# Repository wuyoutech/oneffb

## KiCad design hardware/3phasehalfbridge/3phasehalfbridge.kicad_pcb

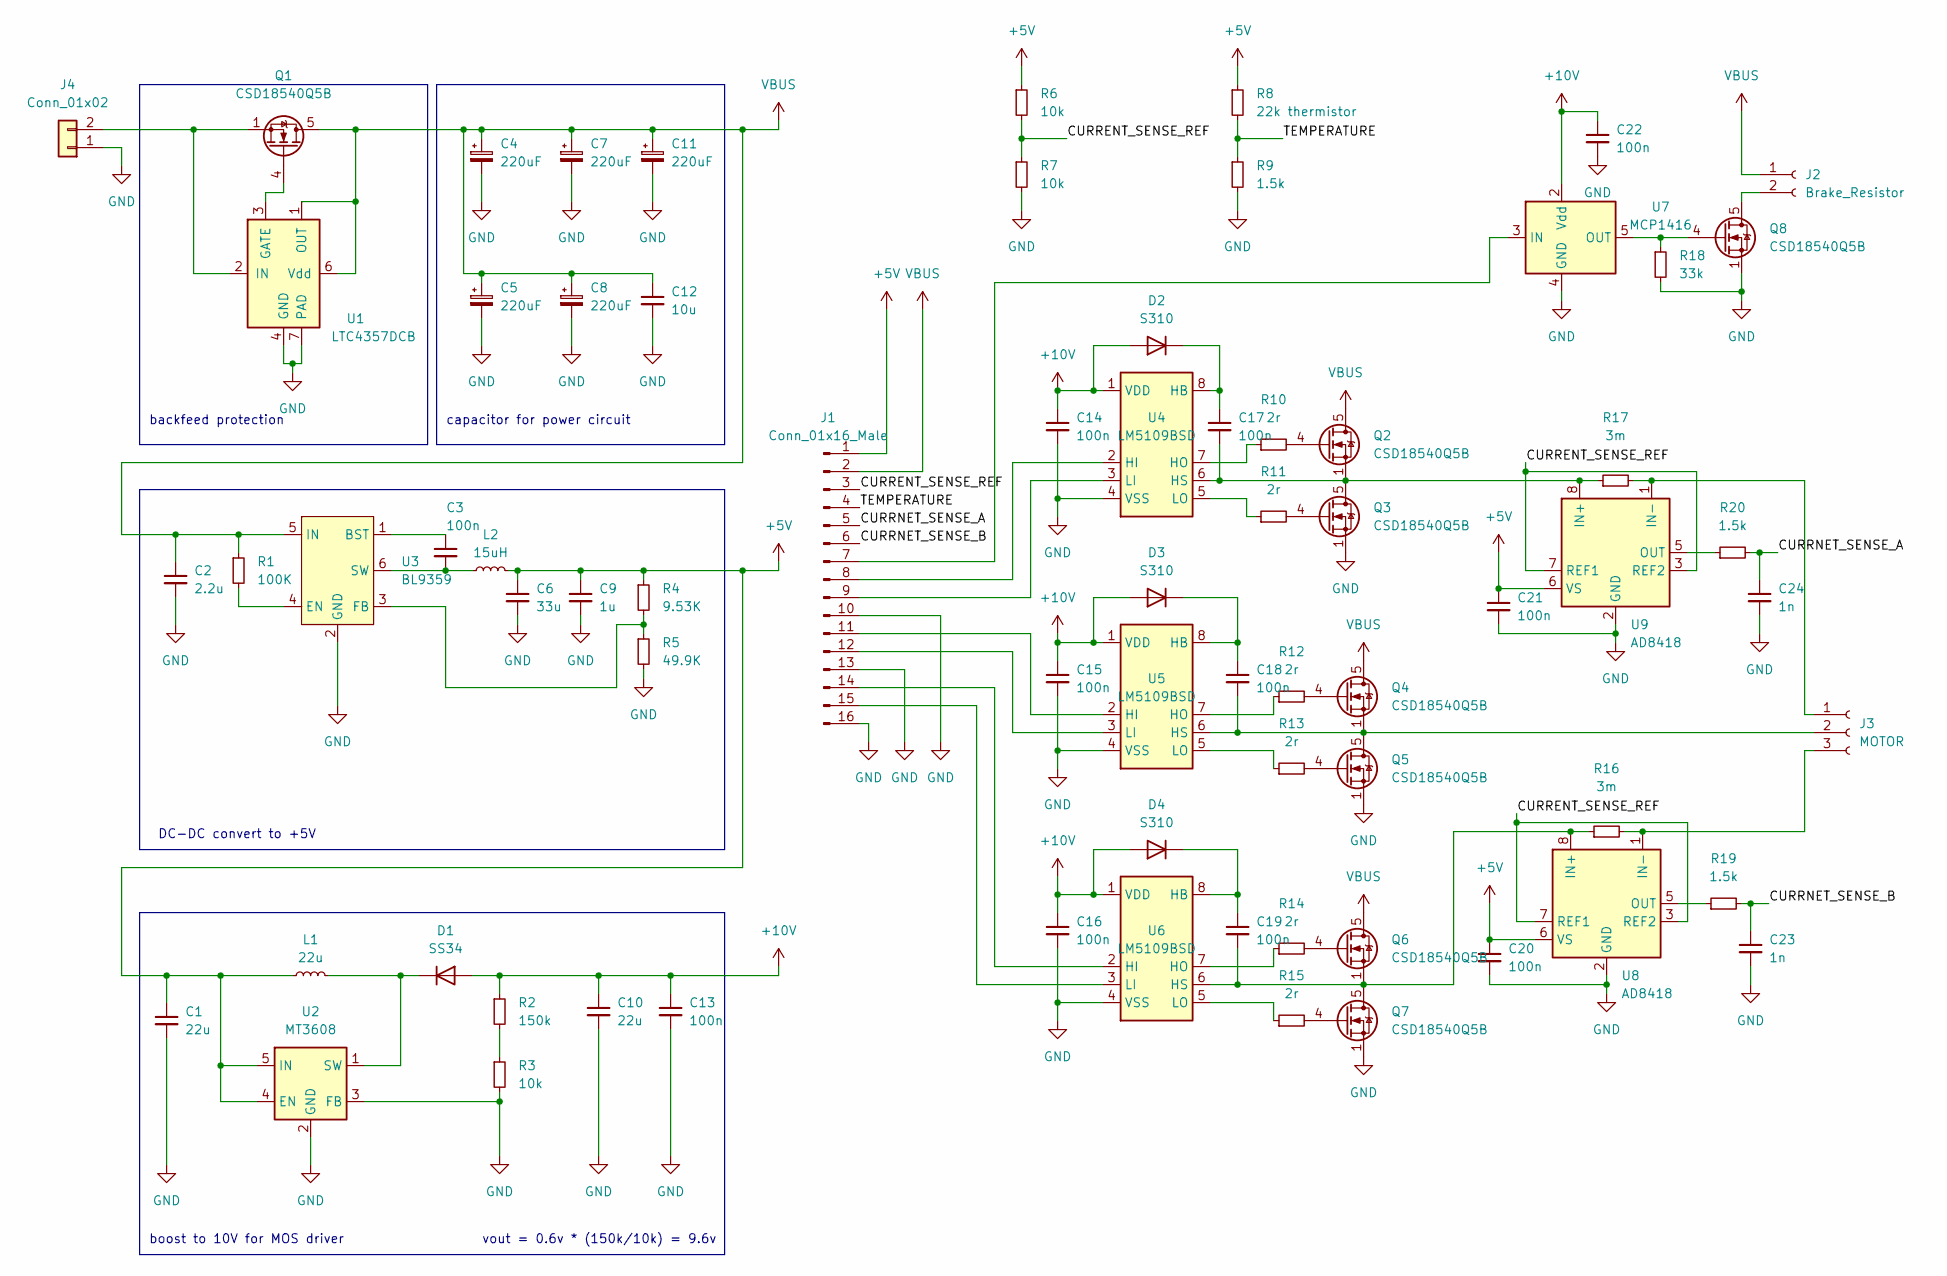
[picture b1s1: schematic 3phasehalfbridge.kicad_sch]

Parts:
C1: 22u; C_0805_2012Metric
C2: 2.2u; C_0805_2012Metric
C3, C13, C14, C15, C16, C17, C18, C19, C20, C21, C22: 100n; C_0402_1005Metric
C4, C5, C7, C8, C11: 220uF; CP_Elec_6.3x3.9
C6: 33u; C_0805_2012Metric
C9: 1u; C_0402_1005Metric
C10: 22u; C_0603_1608Metric
C12: 10u; C_0603_1608Metric
C23, C24: 1n; C_0402_1005Metric
D1: SS34; D_SOD-123F
D2, D4: S310; D_SOD-123F
D3: S310; D_DO-41_SOD81_P10.16mm_Horizontal
J1: Conn_01x16_Male; PinHeader_1x16_P2.54mm_Vertical
J2: Brake_Resistor; SolderWire-1.5sqmm_1x02_P7.8mm_D1.7mm_OD3.9mm
J3: MOTOR; AMASS_MR30PW-FB_1x03_P3.50mm_Horizontal
J4: Conn_01x02; AMASS_XT30PW-M_1x02_P2.50mm_Horizontal
L1: 22u; L_Taiyo-Yuden_MD-5050
L2: 15uH; L_Taiyo-Yuden_MD-5050
Q1, Q2, Q3, Q4, Q5, Q6, Q7, Q8: CSD18540Q5B; TDSON-8-1
R1: 100K; R_0402_1005Metric
R2: 150k; R_0402_1005Metric
R3, R6, R7: 10k; R_0402_1005Metric
R4: 9.53K; R_0402_1005Metric
R5: 49.9K; R_0402_1005Metric
R8: 22k thermistor; R_0402_1005Metric
R9, R19, R20: 1.5k; R_0402_1005Metric
R10, R11, R12, R13, R14, R15: 2r; R_0402_1005Metric
R16, R17: 3m; R_2512_6332Metric
R18: 33k; R_0402_1005Metric
U1: LTC4357DCB; DFN-6-1EP_3x2mm_P0.5mm_EP1.65x1.35mm
U2: MT3608; SOT-23-6
U3: BL9359; SOT-23-6
U4, U5, U6: LM5109BSD; WSON-8-1EP_4x4mm_P0.8mm_EP2.6x3mm
U7: MCP1416; SOT-23-5
U8, U9: AD8418; MSOP-8_3x3mm_P0.65mm

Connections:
+5V: C1.1, C6.1, C9.1, C20.1, C21.1, J1.1, L1.1, L2.2, R4.1, R6.1, R8.1, U2.4 (EN), U2.5 (IN), U8.6 (VS), U9.6 (VS)
+10V: C10.1, C13.1, C14.1, C15.1, C16.1, C22.1, D1.2 (A), D2.2 (A), D3.2 (A), D4.2 (A), R2.1, U4.1 (VDD), U5.1 (VDD), U6.1 (VDD), U7.2 (Vdd)
/CURRENT_SENSE_REF: J1.3, R6.2, R7.1, U8.3 (REF2), U8.7 (REF1), U9.3 (REF2), U9.7 (REF1)
/CURRNET_SENSE_A: C24.1, J1.5, R20.2
/CURRNET_SENSE_B: C23.1, J1.6, R19.2
/TEMPERATURE: J1.4, R8.2, R9.1
GND: C1.2, C2.2, C4.2, C5.2, C6.2, C7.2, C8.2, C9.2, C10.2, C11.2, C12.2, C13.2, C14.2, C15.2, C16.2, C20.2, C21.2, C22.2, C23.2, C24.2, J1.10, J1.13, J1.16, J4.1, Q3.1 (S), Q3.2 (S), Q3.3 (S), Q5.1 (S), Q5.2 (S), Q5.3 (S), Q7.1 (S), Q7.2 (S), Q7.3 (S), Q8.1 (S), Q8.2 (S), Q8.3 (S), R3.2, R5.2, R7.2, R9.2, R18.2, U1.4 (GND), U1.7 (PAD), U2.2 (GND), U2.3 (FB), U3.2 (GND), U4.4 (VSS), U4.9 (VSS), U5.4 (VSS), U5.9 (VSS), U6.4 (VSS), U6.9 (VSS), U7.4 (GND), U8.2 (GND), U9.2 (GND)
unnamed: C3.1, U3.1 (BST)
unnamed: C3.2, L2.1, U3.6 (SW)
unnamed: C17.1, D2.1 (K), U4.8 (HB)
unnamed: C17.2, Q2.1 (S), Q2.2 (S), Q2.3 (S), Q3.5 (D), R17.1, U4.6 (HS), U9.8 (IN+)
unnamed: C18.1, D3.1 (K), U5.8 (HB)
unnamed: C18.2, J3.2, Q4.1 (S), Q4.2 (S), Q4.3 (S), Q5.5 (D), U5.6 (HS)
unnamed: C19.1, D4.1 (K), U6.8 (HB)
unnamed: C19.2, Q6.1 (S), Q6.2 (S), Q6.3 (S), Q7.5 (D), R16.1, U6.6 (HS), U8.8 (IN+)
unnamed: D1.1 (K), L1.2, U2.1 (SW)
unnamed: J1.7, U7.3 (IN)
unnamed: J1.8, U4.2 (HI)
unnamed: J1.9, U4.3 (LI)
unnamed: J1.11, U5.2 (HI)
unnamed: J1.12, U5.3 (LI)
unnamed: J1.14, U6.2 (HI)
unnamed: J1.15, U6.3 (LI)
unnamed: J2.2, Q8.5 (D)
unnamed: J3.1, R17.2, U9.1 (IN-)
unnamed: J3.3, R16.2, U8.1 (IN-)
unnamed: J4.2, Q1.1 (S), Q1.2 (S), Q1.3 (S), U1.2 (IN)
unnamed: Q1.4 (G), U1.3 (GATE)
unnamed: Q2.4 (G), R10.2
unnamed: Q3.4 (G), R11.2
unnamed: Q4.4 (G), R12.2
unnamed: Q5.4 (G), R13.2
unnamed: Q6.4 (G), R14.2
unnamed: Q7.4 (G), R15.2
unnamed: Q8.4 (G), R18.1, U7.5 (OUT)
unnamed: R1.2, U3.4 (EN)
unnamed: R2.2, R3.1
unnamed: R4.2, R5.1, U3.3 (FB)
unnamed: R10.1, U4.7 (HO)
unnamed: R11.1, U4.5 (LO)
unnamed: R12.1, U5.7 (HO)
unnamed: R13.1, U5.5 (LO)
unnamed: R14.1, U6.7 (HO)
unnamed: R15.1, U6.5 (LO)
unnamed: R19.1, U8.5 (OUT)
unnamed: R20.1, U9.5 (OUT)
VBUS: C2.1, C4.1, C5.1, C7.1, C8.1, C11.1, C12.1, J1.2, J2.1, Q1.5 (D), Q2.5 (D), Q4.5 (D), Q6.5 (D), R1.1, U1.1 (OUT), U1.6 (Vdd), U3.5 (IN)

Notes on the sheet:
boost to 10V for MOS driver
backfeed protection
capacitor for power circuit
vout = 0.6v * (150k/10k) = 9.6v
DC-DC convert to +5V

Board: 4 copper layers, 71 parts (0 on the bottom side), 47 nets, no tracks yet.

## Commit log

2022-04-27 add power sch
2022-04-27 move hardware file to subfolder
2022-04-27 finish power tree
2022-04-27 remove track for fp cache file
2022-04-27 add motor sch, move gate driver to motor sch
2022-04-28 add 1.8v LDO for TMC4671 core
2022-04-28 finish motor driver sch
2022-04-29 update git ignore
2022-04-29 create firmware structure
2022-05-03 add firmware
2022-05-05 remove usb lib,use tinyusb instead
2022-05-05 port usb
2022-05-10 fix bug as running 168MHz on stm32f411
2022-05-10 update vscode settings
2022-05-10 move debug usart to usart1, fix small issue
2022-05-10 update system clock config
2022-05-10 update gitignore for hax&bin file
2022-05-10 fix small issue
2022-05-10 add make flash
2022-05-11 update project, has been implement cdc based on tinyusb examples
2022-05-13 remove unused IO init, remove clock config copy from HAL lib, use StdPeriph clock config instead.
2022-05-16 move 3phase halfbridge to independent board
2022-05-16 create sch
2022-05-16 implement RNDIS interface, Tested
2022-05-16 finish usb_descriptors changes
2022-05-20 Enable HID
2022-05-20 combine HID and RNDIS, remove unused CDC interface
2022-05-20 fix button input issue
2022-05-20 change debug interface to jtag/swd
2022-05-20 change HID interace from keyboard to joystick
2022-05-23 change usb hid descriptor to custom, add out EP, change freshrate to 1ms
2022-05-23 change usb update rate in main loop
2022-05-25 add physical usb interface
2022-05-25 remove unused callback for CDC serial
2022-05-30 rename folder
2022-05-30 add cc2544 project
2022-09-16 remove hardware from this repo
2022-09-16 update submodule path
2022-09-16 update gitignore
2022-09-16 remove vscode settings, move systick functions to dedicated files
2022-09-17 move functions to independence files, clean code, NOTE: usb descriptor file not included yet
2022-09-17 add usb desctiptors
2022-09-20 add cdc read and write buff
2022-09-20 update USB callback comments
2022-10-25 [bugfix] add DS_Store file to gitignore
